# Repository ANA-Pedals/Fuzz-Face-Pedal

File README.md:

https://docs.google.com/document/d/1rRPdb6qVqWFwWbFdMLrPitkWkwnEDBBc_jRhgOyyxEs/edit?tab=t.0 
^Link to Documentation

https://docs.google.com/spreadsheets/d/1uSOwf0nW740PyzCEoDDXH0rGgghISvFnG9C1whraXBo/edit?gid=0#gid=0
^Link to Parts List

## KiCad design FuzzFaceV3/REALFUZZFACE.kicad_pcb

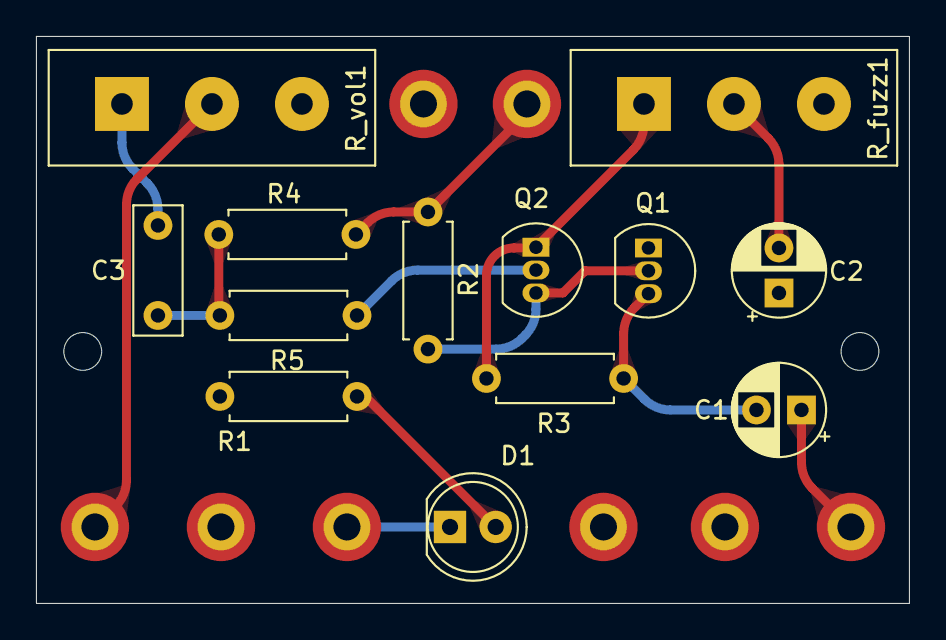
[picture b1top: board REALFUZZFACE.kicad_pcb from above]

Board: 2 copper layers, 48.5 x 31.5 mm, 23 parts (0 on the bottom side), 13 nets.

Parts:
C1: 2.2uF; StandardPolarizedCapacitorPedal
C2: 20uF; StandardPolarizedCapacitorPedal
C3: 0.01uF; StandardUnpolarizedCapacitorPedal
D1: LED; LED_D5.0mm_Clear
GND1: GND; 1.5mm_MountingHole
IN1: IN; 1.5mm_MountingHole
IN_GND1: IN_GND; 1.5mm_MountingHole
MH1: MH1; MountingHole_2.1mm
MH2: MH2; MountingHole_2.1mm
OUT1: OUT; 1.5mm_MountingHole
OUT_GND1: OUT_GND; 1.5mm_MountingHole
PWR1: PWR; 1.5mm_MountingHole
P_GND1: P_GND; 1.5mm_MountingHole
Q1, Q2: 2SA1015; TO-92_Inline
R1: 4.7k; StandardResistorPedal
R2: 33k; StandardResistorPedal
R3: 100k; StandardResistorPedal
R4: 470; StandardResistorPedal
R5: 8.2k; StandardResistorPedal
R_fuzz1: 1k; ANAPot
R_vol1: 500k; ANAPot
SW1: SW; 1.5mm_MountingHole

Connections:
GND: C2.1, GND1.1, IN_GND1.1, OUT_GND1.1, Q1.1 (E), R1.1, R_fuzz1.3, R_vol1.3
unnamed: C1.1, IN1.1
unnamed: C2.2, R_fuzz1.2
unnamed: C3.1, R4.2, R5.1
unnamed: C3.2, R_vol1.1
unnamed: D1.2 (A), R1.2
unnamed: D1.1 (K), SW1.1
unnamed: OUT1.1, R_vol1.2
unnamed: PWR1.1, R2.1, R4.1
unnamed: C1.2, Q1.3 (B), R3.1
unnamed: Q1.2 (C), Q2.3 (B), R2.2
unnamed: Q2.2 (C), R5.2
unnamed: Q2.1 (E), R3.2, R_fuzz1.1

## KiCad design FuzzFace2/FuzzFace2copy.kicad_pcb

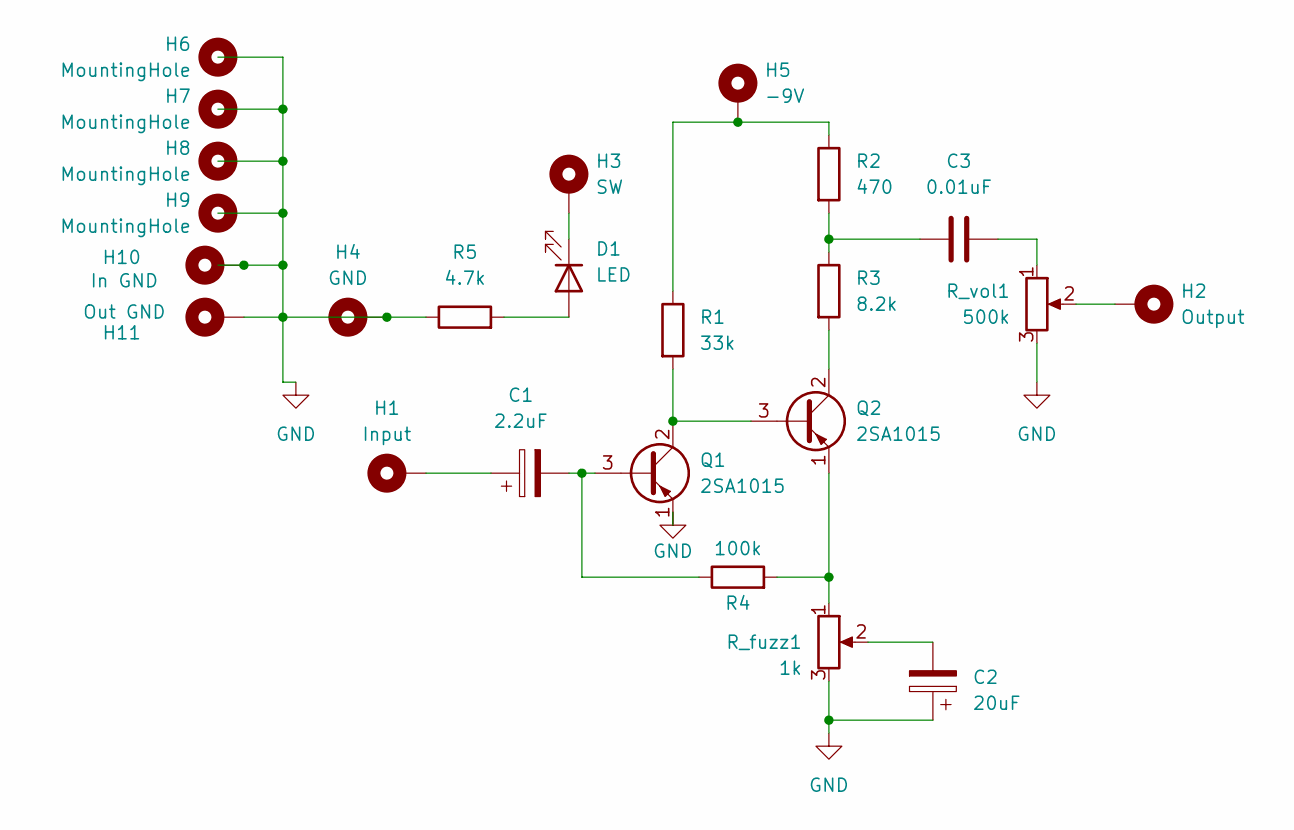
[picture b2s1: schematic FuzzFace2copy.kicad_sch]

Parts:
C1: 2.2uF; StandardPolarizedCapacitorPedal
C2: 20uF; StandardPolarizedCapacitorPedal
C3: 0.01uF; StandardUnpolarizedCapacitorPedal
D1: LED; LED_D5.0mm_Clear
H1: Input; 1.5mm_MountingHole
H2: Output; 1.5mm_MountingHole
H3: SW; 1.5mm_MountingHole
H4: GND; 1.5mm_MountingHole
H5: -9V; 1.5mm_MountingHole
H6, H7, H8, H9: MountingHole; MountingHole_2.2mm_M2_DIN965_Pad_TopOnly
H10: In GND; 1.5mm_MountingHole
H11: Out GND; 1.5mm_MountingHole
Q1, Q2: 2SA1015; TO-92_Inline
R1: 33k; StandardResistorPedal
R2: 470; StandardResistorPedal
R3: 8.2k; StandardResistorPedal
R4: 100k; StandardResistorPedal
R5: 4.7k; StandardResistorPedal
R_fuzz1: 1k; StandardPot
R_vol1: 500k; StandardPot

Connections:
GND: C2.1, H4.1, H10.1, H11.1, Q1.1 (E), R5.1, R_fuzz1.3, R_vol1.3
unnamed: C1.1, H1.1
unnamed: C2.2, R_fuzz1.2
unnamed: C3.1, R2.2, R3.1
unnamed: C3.2, R_vol1.1
unnamed: D1.2 (A), R5.2
unnamed: D1.1 (K), H3.1
unnamed: H2.1, R_vol1.2
unnamed: H5.1, R1.1, R2.1
unnamed: C1.2, Q1.3 (B), R4.1
unnamed: Q1.2 (C), Q2.3 (B), R1.2
unnamed: Q2.2 (C), R3.2
unnamed: Q2.1 (E), R4.2, R_fuzz1.1

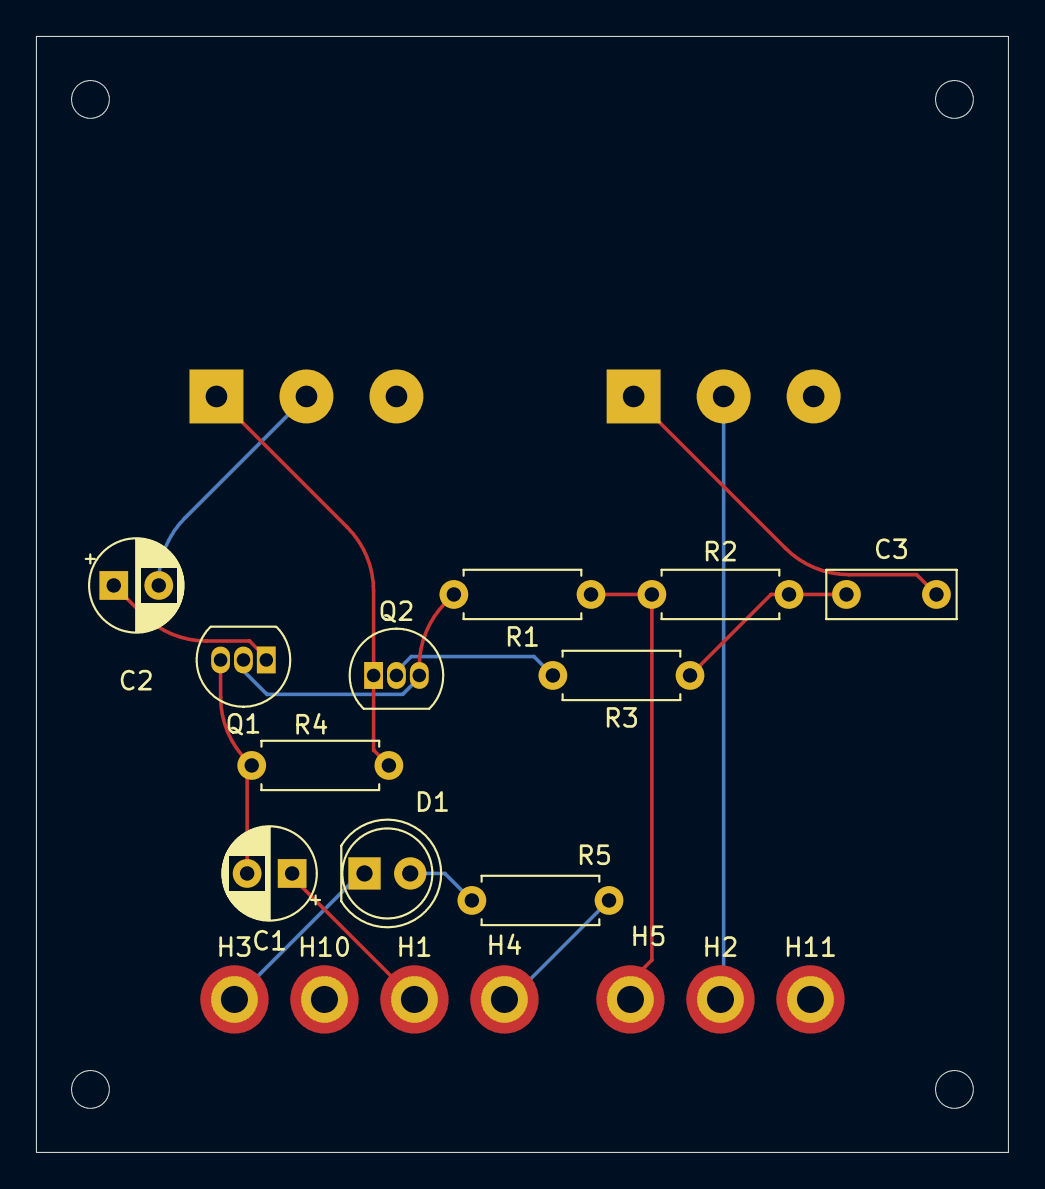
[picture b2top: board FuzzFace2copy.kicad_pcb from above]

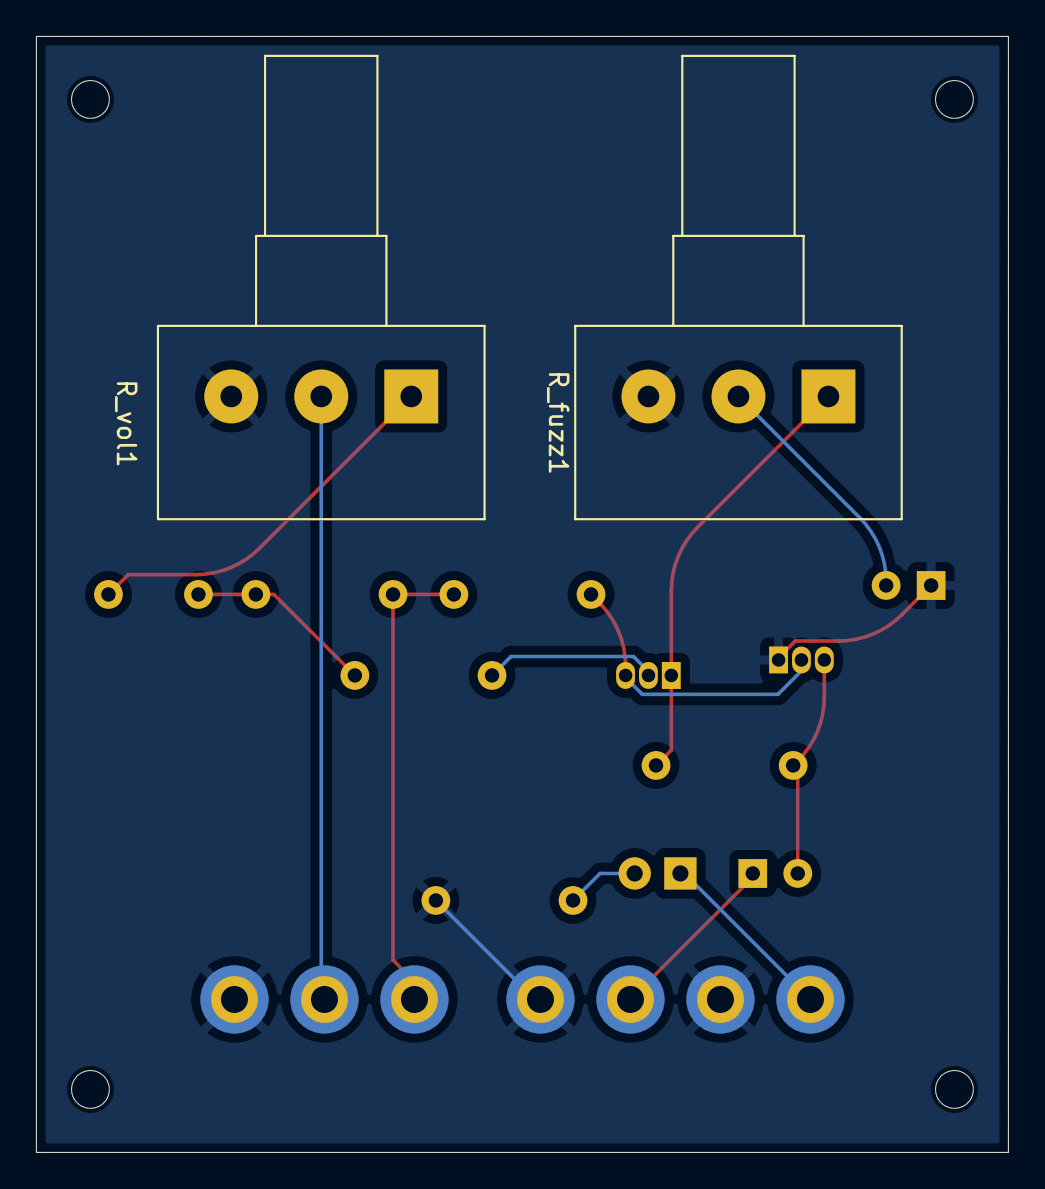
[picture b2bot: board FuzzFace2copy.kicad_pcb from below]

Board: 2 copper layers, 54.0 x 62.0 mm, 24 parts (2 on the bottom side), 13 nets.

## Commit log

2025-01-17 Added Kicad Project
2025-01-18 Austin's Fuzz Face PCB Design
2025-09-07 fuzz face v2 files
2025-09-08 done
2025-09-08 Revision Nolan
